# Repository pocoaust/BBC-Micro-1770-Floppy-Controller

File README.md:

# BBC-Micro-1770-Floppy-Controller

This is a 1770 standard floppy controller for the BBC Micro.  If you ended up with an OPUS
or other type of controller and want to go back to vanilla BBC 1770 or just build a 
BBC 1770 controller this is for you.

Fitting instructions as per Acorn_1770DiskIFUpgrade.pdf

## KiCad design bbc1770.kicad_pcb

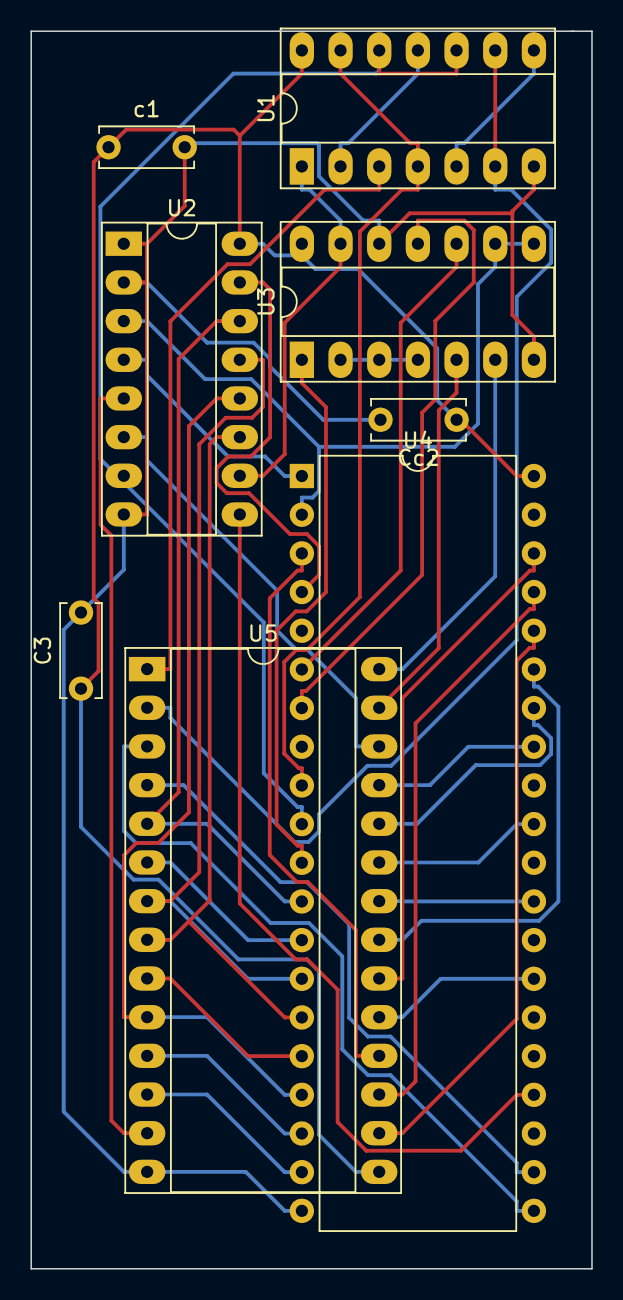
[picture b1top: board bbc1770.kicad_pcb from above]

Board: 2 copper layers, 36.8 x 81.3 mm, 8 parts (0 on the bottom side), 41 nets.

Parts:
C3: 100nf; C_Disc_D6.0mm_W2.5mm_P5.00mm
Cc2: 100nf; C_Disc_D6.0mm_W2.5mm_P5.00mm
U1: 74LS00; DIP-14_W7.62mm_Socket_LongPads
U2: 74LS173; DIP-16_W7.62mm_Socket_LongPads
U3: 74LS02; DIP-14_W7.62mm_Socket_LongPads
U4: 8271; DIP-40_W15.24mm
U5: WD1772; DIP-28_W15.24mm_Socket_LongPads
c1: 100nf; C_Disc_D6.0mm_W2.5mm_P5.00mm

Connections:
/A3: U4.21 (A0), U5.3 (A0)
/A4: U4.22 (A1), U5.4 (A1)
/D0: U2.14 (D0), U4.12 (DB0), U5.5 (DI0)
/D1: U4.13 (DB1), U5.6 (DI1)
/D2: U2.13 (D1), U4.14 (DB2), U5.7 (DI2)
/D3: U2.11 (D3), U4.15 (DB3), U5.8 (DI3)
/D4: U4.16 (DB4), U5.9 (DI4)
/D5: U2.12 (D2), U4.17 (DB5), U5.10 (DI5)
/D6: U4.18 (DB6), U5.11 (DI6)
/D7: U4.19 (DB7), U5.12 (DI7)
/RESET: U2.5 (Q2), U5.13 (~MR)
/WR: U1.6, U1.9, U5.2 (R/~W)
GND: C3.2, Cc2.2, U1.7, U2.1 (Oe1), U2.2 (Oe2), U2.8 (GND), U3.7, U3.12, U4.20 (GND), U5.14 (GND), c1.2
unnamed: U1.1, U2.10 (E2), U3.13
unnamed: U1.3, U5.1 (~CS)
unnamed: U1.5, U1.8
unnamed: U1.10, U1.12, U2.7 (Cp), U4.10 (WR)
unnamed: U1.2, U1.11
unnamed: U1.4, U1.13, U4.9 (~RD)
unnamed: U2.3 (Q0), U3.8, U3.9, U4.2 (Select_0)
unnamed: U2.4 (Q1), U4.1 (Fault_Reset)
unnamed: U2.6 (Q3), U5.26 (~DDEN)
unnamed: U2.9 (E1), U4.24 (CS)
unnamed: U2.15 (Mr), U4.4 (RESET)
unnamed: U3.1, U4.11 (INT)
unnamed: U3.2, U3.3, U3.4
unnamed: U3.5, U5.27 (DRQ)
unnamed: U3.6, U5.28 (INTRQ)
unnamed: U3.10, U4.6 (Select_1)
unnamed: U3.11, U4.7 (DACK)
unnamed: U4.3 (4Mhz_clk), U5.18 (CLK)
unnamed: U4.27 (UNSEP_Data), U5.19 (~RD)
unnamed: U4.29 (Fault), U5.22 (WD)
unnamed: U4.31 (TRK0), U5.23 (~TR00)
unnamed: U4.33 (Write_Protect), U5.25 (~WPRT)
unnamed: U4.34 (Index), U5.24 (~IP)
unnamed: U4.35 (WR_enable), U5.21 (WG)
unnamed: U4.36 (Seek/step), U5.16 (STEP)
unnamed: U4.37 (Direction), U5.17 (DIRC)
unnamed: U4.38 (Load_hd), U5.20 (MOTOR)
VCC: C3.1, Cc2.1, U1.14, U2.16 (VCC), U3.14, U4.40 (VDD), U5.15 (VCC), c1.1
